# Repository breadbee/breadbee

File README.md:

# Breadbee

A very small, 32mm x 30mm, ARM Cortex A7 development board that costs about ~$10
to make in low quantities and can be assembled at home with a cheap hot air rework
station. With a [small adapter socket](./hivee) it can be mounted vertically in a standard breadboard.

The breadbee is based on a relatively unknown IP camera SoC, the MSC313E, from a company called MStar
(now part of MediaTek as a subsidiary called SigmaStar).
You might have never heard of MStar but you probably have one of their chips in your TV.

## Features

These are features that are working:

- ~1GHz Cortex A7 CPU with NEON etc[0].
- 64MB DDR2 (Probably DDR2-1333)
- 128KB SRAM (88KB if you use a MSC313(no e).
- [Bootable, memory mapped SPI-NOR](https://github.com/fifteenhex/linux/blob/msc313e/drivers/spi/spi-msc313-isp.c)
- 100Mbit ethernet.
- [4 x 10bit ADC channels](https://github.com/fifteenhex/linux/blob/msc313e/drivers/iio/adc/msc313e_sar.c)
- [2 x SPI](https://github.com/fifteenhex/linux/blob/msc313e/drivers/spi/spi-msc313.c)
- [1 x I2C (there is possibly one more)](https://github.com/fifteenhex/linux/blob/msc313e/drivers/i2c/busses/i2c-msc313e.c)
- [3 UARTs](https://github.com/fifteenhex/linux/blob/b3c521f8f30c9cc6f9f9c5c87429336d4756dcca/drivers/tty/serial/8250/8250_dw.c#L751) [1]
- Lots of GPIO. At least one pin with wake up support.
- [RTC](https://github.com/fifteenhex/linux/blob/msc313e/drivers/rtc/rtc-msc313e.c)
- [WDT](https://github.com/fifteenhex/linux/blob/msc313e/drivers/watchdog/msc313e_wdt.c)
- [3 x Timer](https://github.com/fifteenhex/linux/blob/msc313e/drivers/clocksource/timer-msc313e.c)
- [8 x PWM](https://github.com/fifteenhex/linux/blob/msc313e/drivers/pwm/pwm-msc313e.c)
- [SD/SDIO interface](https://github.com/fifteenhex/linux/blob/msc313e/drivers/mmc/host/mstar-fcie.c)
- 2 x ["byte" dma controller](https://github.com/fifteenhex/linux/blob/msc313e/drivers/dma/mstar/mstar-msc313-bdma.c)
- USB PHY
- USB host/device mux
- Faraday FUSBH200 USB *ehci* host controller
- On die temperature sensor. (sorta)
- Hardware RNG. (quality unknown)
- SHA engine. (Runs, not wired to the kernel)
- 8051 "house keeping" MCU. (Basic remoteproc driver)

[0] MStar says it's 800MHz but their own cpufreq code says they clock it to 1GHz
Clocking up to 1.1GHz works fine running dhrystone for hours but causes random lock ups if the spi nor controller and ethernet are fighting for bus access.
[1] One UART is used by the serial console, two more are available via muxing. 

 The chip has a bunch of stuff in it that isn't supported yet:
 - [MUSB USB device controller](https://github.com/fifteenhex/linux/blob/msc313e/drivers/usb/musb/mstar.c)
 - Camera interface, h264 encoder, mjpeg etc.
 - Audio ADC/DAC
 - [Crypto engine](https://github.com/fifteenhex/linux/blob/msc313e/drivers/crypto/msc313-aesdma.c) that seems to be able to do AES encrypted DMA transfers, memory mapped AES encryption etc
 - Some sort of IR decoder that can wake the chip up based on the IR codes it sees.
 - 6 byte unique device ID and efuse for key storage
 - [command queue dma controller](https://github.com/fifteenhex/linux/blob/msc313e/drivers/dma/mstar/mstar-msc313-cmdq.c)

It's full of flashy magic!

## Power consumption

According to a Kyoritsu KEW 1062 inline with the vbus of a usb cable:

| state        | Ethernet on | RTC wake | value |
|--------------|-------------|----------|-------|
| Booted idle  | yes         | N/A      | 138mA |
| Booted idle  | no          | N/A      | 113mA |
| Memory sleep |             | Yes      | 12mA  |

## Board Revisions

- Rev0 - Original version, works.
- Rev1 - Same as rev0 basically but the QFN80 footprint is slightly fixed to not have very thin pads on one side. Rev1 has one weird pad on the QFN80 footprint and an overlapping extra trace on one of the USB signals.

## Motivations

- Networked microcontrollers are a disaster waiting to happen; Many solutions - even commercial ones - use LWIP as the TCP/IP stack with no intention of actually maintaining it, use relatively unknown TLS libraries because of lack of memory, have no memory protection, no isolation between the moving parts.

- There are no solutions yet that can run a real OS like Linux that can be integrated by hobbyists into boards from cheap PCB vendors that don't have show stopping limitations. I.e. the AllWinner V3s is very similar to the SoC used here but it only has one SPI controller that is lost as soon as you put SPI NOR on it. The MSC313E has just enough of the usual microcontroller peripherals to make it useful, comes in a (relatively) easy to work with QFN package, is tiny and costs ~$4.
It is a bit harder to integrate into your designs than a microcontroller that requires a single power supply but all of the information you would need to do so is right here. The schematic for the breadbee is incredibly simple.

- There are single board computers out there that have more cores, more memory etc and are still around $10 but they are over kill for applications where even an ESP32 has enough horse power and they aren't usually something you can integrate into your project without reserving considerable space.

- Why not? The MSC313E is a Cortex-A so getting Linux running from scratch was relatively simple. The peripherals are super weird in places but not totally insane.

## But where's the WiFi!>!!111

The breadbee is meant to be a "minimum viable product" to get the ball rolling. It's impossible to write drivers for the SDIO controller or USB needed for WiFi without a platform to work on. Breadbee is that platform. Once SDIO works there will be an Ampak AP6212 based module to add wifi to breadbees and maybe a respin of the breadbee with the ethernet jack replaced with an Ampak module. 

A simpler alternative consists in using an already supported USB-to-WiFi PCB module given that the breadbee's USB host controller already works fine. This project is .

## Can I have one.. where do I get the chips..

- If you ask very nicely and you are willing to do something like write a nice python library or flesh out drivers for the board it's possible you can have one of the prototype boards for FREE! Get in touch!

- ~~If you just want to buy one the intention is to put the board up on a crowd sourcing site at some point. When that happens that information will be here.~~ [crowdsupply](https://www.crowdsupply.com/daniel-palmer/breadbee) will eventually be selling premade boards. This might take a while though.

- If you want chips to integrate into your own projects and don't have contacts in Shenzhen to get them get in touch and we'll figure something out. If you want 2080 of them getting them isn't a problem. If you want one or two I have a small supply. If the crowd sourcing happens and there is enough money left to buy extra chips to distribute in more accessible ways I will. Since April 2020 chips have now also started to turn on up ebay.

- The gerbers have been uploaded to [OSH park (rev1)](https://oshpark.com/shared_projects/lQ6wt3Dk) ready to order. [OSH park (rev0)](https://oshpark.com/shared_projects/slorKWK0)

## Software

Note that this is all in flux right at the moment. These repos are getting rebase'd fairly often.

### U-boot

There is a basic port of u-boot that so far take over from the MStar IPL and load a kernel from the SPI NOR, write it etc.
See boot process below for more details.

https://github.com/fifteenhex/u-boot/tree/msc313

### Kernel

All of the above features work to some degree in the work tree. Mainlining is in progress but will take time.
For more info please see the linux-chenxing.org [page about mainlining](http://linux-chenxing.org/mainlining.html).

### Buildroot

Combines the u-boot and kernel above with a root filesystem and generates flashable images.
There are some small pieces of a board configuration application called "beecfg" to setup pinmuxing etc.

https://github.com/fifteenhex/breadbee_buildroot

## BoM

[Google Sheet](https://docs.google.com/spreadsheets/d/1FwoQdfAULd6vKPnkrVnFDfQQs8OdsqdwefH3aLVehPo)

## Pin Table

### J2 - Main 2.54mm header

| interrupt | 5v tolerant |   notes   | alt functions           |    name   |  # |  # |   name    | alt functions           |   notes                 | 5v tolerant | interrupt |
|-----------|-------------|-----------|-------------------------|-----------|----|----|-----------|-------------------------|-------------------------|-------------|-----------|
|           |             |           |                         |    +5v    |  1 | 2  |   +3v3    |                         |                         |             |           |
|           |             |           |                         |    gnd    |  3 | 4  | pm_gpio4  |                         | [0]                     |    yes      |   yes     |
|           |             |           |                         | i2c1_scl  |  5 | 6  | i2c1_sda  |                         |                         |             |           |
|   yes     |             |           | ej_tck, pwm4            | spi0_cz   |  7 | 8  | spi0_ck   | ej_tms, pwm5            |                         |             |   yes     |
|   yes     |             |           | ej_tdo, pwm6            | spi0_di   |  9 | 10 | spi0_do   | ej_tdi, pwm7            |                         |             |   yes     |
|           |     yes     |           |                         | sar_gpio2 | 11 | 12 | sar_gpio3 |                         |                         |    yes      |           |
|           |     yes     |           |                         | sar_gpio1 | 13 | 14 | sar_gpio0 |                         |                         |    yes      |           |
|           |     yes     |   cs      | spi0_cz, pwm0           | fuart_rx  | 15 | 16 | fuart_tx  | spi0_ck, pwm1           |   clk                   |    yes      |           |
|           |     yes     | mosi, [1] | spi0_di, pwm2, uart1_rx | fuart_cts | 17 | 18 | fuart_rts | spi0_do, pwm3, uart1_tx |   miso                  |    yes      |           |
|           |             |           |                         | sr_io7    | 19 | 20 | sr_io6    |                         |                         |             |           |
|           |             |           |                         | sr_io5    | 21 | 22 | sr_io4    |                         |                         |             |           |
|           |             |           |                         | sr_io3    | 23 | 24 | sr_io2    |                         |                         |             |           |

0: This is a special pin that has to be explictly unlocked to be set. It seems to be intended for powering down the main CPU. It might move on rev1.

1 - When fuart is mux'd in it's also possible to mux'in uart1 and get a working rx only
    second uart here.

### J4 - Misc/High speed interfaces

* Note the USB and SD/SDIO are not guaranteed to work as literally no care was taken to route those signals properly on rev0. 

| name      | #  | alt functions | 5v tolerant | interrupt | notes |
|-----------|----|---------------|-------------|-----------|-------|
| +3v3      | 1  |               |             |           |       |
| sd_d3     | 2  |   spi1_do     | yes         |           | miso  |
| sd_d2     | 3  |   spi1_di     | yes         |           | mosi  |
| sd_d1     | 4  |   spi1_ck     | yes         |           | clk   |
| sd_d0     | 5  |   spi1_cz     | yes         |           | cs    |
| sd_cmd    | 6  |               | yes         |           |       |
| sd_clk    | 7  |               | yes         |           |       |
| pm_sd_cdz | 8  |               |             | yes       |       |
| gnd       | 9  |               |             |           |       |
| +5v       | 10 |               |             |           |       |
| usb_dm    | 11 |               |             |           |       |
| usb_dp    | 12 |               |             |           |       |
| gnd       | 13 |               |             |           |       |
| sr_io15   | 14 |               |             |           |       |
| sr_io14   | 15 |               |             |           |       |
| sr_io13   | 16 |               |             |           |       |
| sr_io12   | 17 |               |             |           |       |
| sr_io11   | 18 |               |             |           |       |
| sr_io10   | 19 |               |             |           |       |
| sr_io9    | 20 |               |             |           |       |
| sr_io8    | 21 |               |             |           |       |

### Test Points

- The audio pins are broken out to a series of test points on the left side of the parts size of the board.
- pm_irin is broken out to a test point on the ethernet jack side of the board.

## Using JTAG

JTAG is enabled at boot up on the spi0 pins by the u-boot SPL.

## More technical info

[linux-chenxing](http://linux-chenxing.org) has more info about mstar/sigmastar socs.

## Articles etc

[A nice blog entry from Willy about his experience building boards](https://wtarreau.blogspot.com/2020/09/breadbee-build-your-own-single-board.html)

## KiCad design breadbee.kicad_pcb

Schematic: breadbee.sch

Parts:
C1, C6, C9, C10, C11, C12, C13, C14, C15, C16, C17, C18, C19, C20, C21, C22, C24, C25, C26, C27, C35, C36, C37, C38: 1uf; C_0402_1005Metric
C2, C3, C4: 220pf; C_0402_1005Metric
C5: 1uF; C_0402_1005Metric
C7, C8: 18pf; C_0402_1005Metric
C23, C28, C29, C30, C31, C32: 10uf; C_0402_1005Metric
C33, C34: 100nf; C_0402_1005Metric
D1, D2: LED_Small; LED_0805_2012Metric
J1: HR961160C
J2: Conn_02x12_Odd_Even; PinHeader_2x12_P2.54mm_Vertical
J3: USB_B_Micro; USB-MICRO-B
J4: Conn_01x21; PinHeader_1x21_P1.00mm_Vertical
L1, L2, L3: 1.5uH; L_Taiyo-Yuden_MD-2020
R1: 200k; R_0402_1005Metric
R2, R3, R18, R21, R22: 100k; R_0402_1005Metric
R4: 150k; R_0402_1005Metric
R5: 510k; R_0402_1005Metric
R6: 110K; R_0402_1005Metric
R7: 1.1m; R_0402_1005Metric
R8, R19, R20: 1m; R_0402_1005Metric
R9, R10: 390; R_0402_1005Metric
R11, R12, R17: 0; R_0402_1005Metric
R13, R14, R15, R16: 22; R_0402_1005Metric
R23: 1.2m; R_0402_1005Metric
TP1, TP2, TP3, TP4, TP5, TP6, TP7: TestPoint; TestPoint_Pad_D1.0mm
U1: msc313e; QFN-80_EP_8x8_Pitch0.35mm
U2: spinor; wson8-8x6mm
U3: ea3036c; UQFN-20-1EP_3x3mm_P0.4mm_EP1.85x1.85mm_ThermalVias
U4: ch340e; MSOP-10_3x3mm_P0.5mm
U5: tvsarray; SOT-23-6
Y1: Crystal_GND24; Crystal_SMD_Abracon_ABM8G-4Pin_3.2x2.5mm

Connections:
+1V0: C3.1, C9.1, C10.1, C11.1, C12.1, C13.1, C20.1, C28.1, L3.2, R3.1, R21.1, U1.5, U1.8, U1.40, U1.60, U1.61, U1.67
+1V8: C2.1, C23.1, C24.1, C25.1, C26.1, L1.1, R1.1, R18.1, U1.3, U1.4, U1.6
+3V3: C4.1, C5.1, C6.1, C14.1, C15.1, C16.1, C17.1, C18.1, C19.1, C29.1, C37.1, J2.2, J4.1, L2.2, R5.1, R11.1, R12.1, R22.1, U1.7, U1.14, U1.27, U1.35, U1.43, U1.62, U2.7, U2.8, U4.7, U4.10, U5.5
+5V: C27.1, C30.1, C31.1, C32.1, J2.1, J3.1 (VBUS), J4.10, R7.1, R19.1, R20.1, U3.7, U3.10, U3.16, U3.19
/console_rx: U1.19, U4.9
/console_tx: U1.18, U4.8
/eth_rn: R15.2, U1.31
/eth_rp: R16.2, U1.32
/eth_tn: R13.2, U1.33
/eth_tp: R14.2, U1.34
/fuart_cts: J2.17, U1.38
/fuart_rts: J2.18, U1.39
/fuart_rx: J2.15, U1.36
/fuart_tx: J2.16, U1.37
/i2c1_scl: J2.5, U1.41
/i2c1_sda: J2.6, U1.42
/led0: R9.1, U1.58
/led1: R10.1, U1.59
/pm_gpio4: J2.4, U1.21
/pm_sd_cdz: J4.8, U1.15
/reset: C37.2, R23.1, U1.17
/sar_gpio0: J2.14, U1.12
/sar_gpio1: J2.13, U1.11
/sar_gpio2: J2.11, U1.10
/sar_gpio3: J2.12, U1.9
/sd_clk: J4.7, U1.68
/sd_cmd: J4.6, U1.69
/sd_d0: J4.5, U1.70
/sd_d1: J4.4, U1.71
/sd_d2: J4.3, U1.72
/sd_d3: J4.2, U1.73
/spi0_ck: J2.8, U1.64
/spi0_cz: J2.7, U1.63
/spi0_di: J2.9, U1.65
/spi0_do: J2.10, U1.66
/spinor_miso: U1.25, U2.2
/spinor_mosi: U1.23, U2.5
/spinor_sck: U1.26, U2.6
/spinor_~cs: U1.22, U2.1
/spinor_~wp: U1.24, U2.3
/sr_io2: J2.24, U1.44
/sr_io3: J2.23, U1.45
/sr_io4: J2.22, U1.46
/sr_io5: J2.21, U1.47
/sr_io6: J2.20, U1.48
/sr_io7: J2.19, U1.49
/sr_io8: J4.21, U1.50
/sr_io9: J4.20, U1.51
/sr_io10: J4.19, U1.52
/sr_io11: J4.18, U1.53
/sr_io12: J4.17, U1.54
/sr_io13: J4.16, U1.55
/sr_io14: J4.15, U1.56
/sr_io15: J4.14, U1.57
/usb_dm: J4.11, U1.75
/usb_dp: J4.12, U1.76
/xtal_in: C7.1, R8.2, U1.28, Y1.1
/xtal_out: C8.1, R8.1, U1.29, Y1.3
GND: C1.2, C5.2, C6.2, C7.2, C8.2, C9.2, C10.2, C11.2, C12.2, C13.2, C14.2, C15.2, C16.2, C17.2, C18.2, C19.2, C20.2, C21.2, C22.2, C23.2, C24.2, C25.2, C26.2, C27.2, C28.2, C29.2, C30.2, C31.2, C32.2, C33.2, C34.2, C35.2, C36.2, C38.2, D1.1, D2.1, J2.3, J3.5 (GND), J4.9, J4.13, R2.2, R4.2, R6.2, R17.2, R18.2, R21.2, R22.2, R23.2, U1.20, U1.81, U2.4, U3.1, U3.4, U3.5, U3.12, U3.13, U3.15, U3.17, U3.21, U4.3, U5.2, Y1.2, Y1.4
unnamed: C1.1, R7.2, U3.18
unnamed: C2.2, R1.2, R2.1, U3.14
unnamed: C3.2, R3.2, R4.1, U3.2
unnamed: C4.2, R5.2, R6.1, U3.3
unnamed: C21.1, R11.2, U1.30
unnamed: C22.1, R12.2, U1.74
unnamed: C33.1, J1.5
unnamed: C34.1, J1.6
unnamed: C35.1, R19.2, U3.9
unnamed: C36.1, R20.2, U3.8
unnamed: C38.1, U1.13
unnamed: D1.2, R9.2
unnamed: D2.2, R10.2
unnamed: J1.3, R14.1, U5.4
unnamed: J1.4, R13.1, U5.6
unnamed: J1.7, R16.1, U5.1
unnamed: J1.8, R15.1, U5.3
unnamed: J1.10, R17.1
unnamed: J3.2 (D-), U4.2
unnamed: J3.3 (D+), U4.1
unnamed: L1.2, U3.11
unnamed: L2.1, U3.6
unnamed: L3.1, U3.20
unnamed: TP1.1, U1.77
unnamed: TP2.1, U1.2
unnamed: TP3.1, U1.78
unnamed: TP4.1, U1.79
unnamed: TP5.1, U1.80
unnamed: TP6.1, U1.1
unnamed: TP7.1, U1.16

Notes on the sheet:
CONSOLE
STATUS LEDS
RESET
yes, reset is active high, this is not a mistake
24MHZ OSC
SPI NOR
USER IO
POWER SUPPLY
ETHERNET
DECOUPLING
These are jumpers to allow the usb and eth power supplies to be disconnected if you don't need them. This seems to actually stop the board from booting though so they might be removed in the next revision.
The enables are configured to sequence the power rails in accordance with the datasheet.

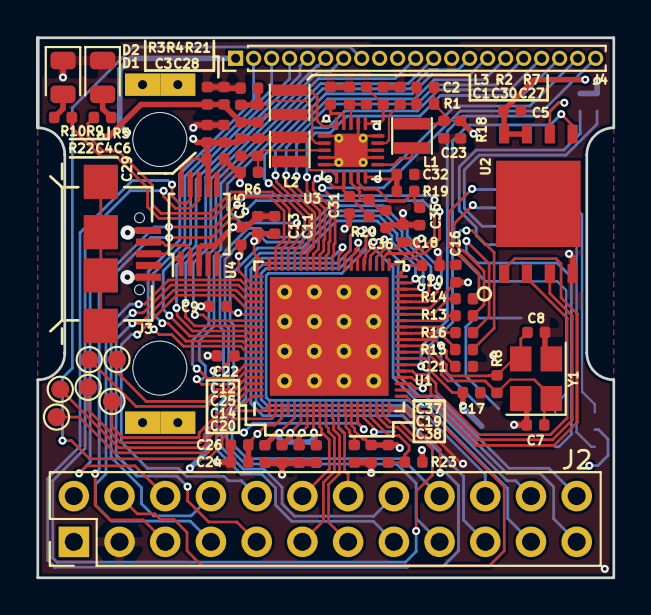
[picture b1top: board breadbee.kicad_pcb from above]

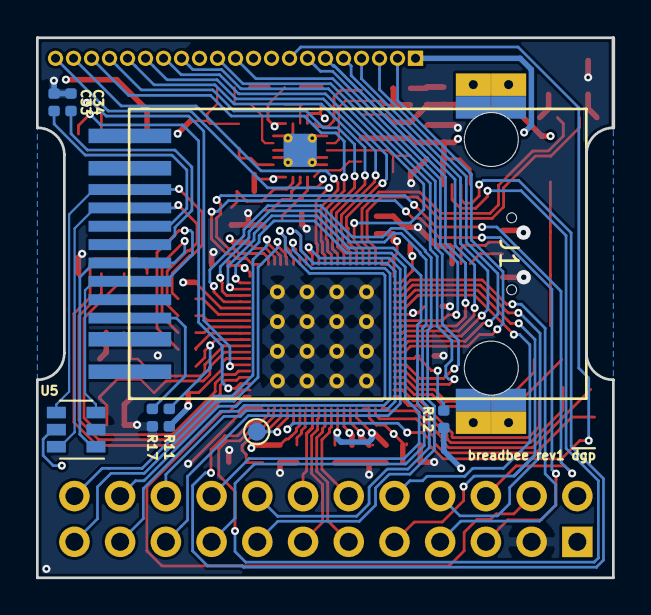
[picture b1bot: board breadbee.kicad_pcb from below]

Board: 4 copper layers, 32.0 x 30.0 mm, 83 parts (8 on the bottom side), 89 nets.

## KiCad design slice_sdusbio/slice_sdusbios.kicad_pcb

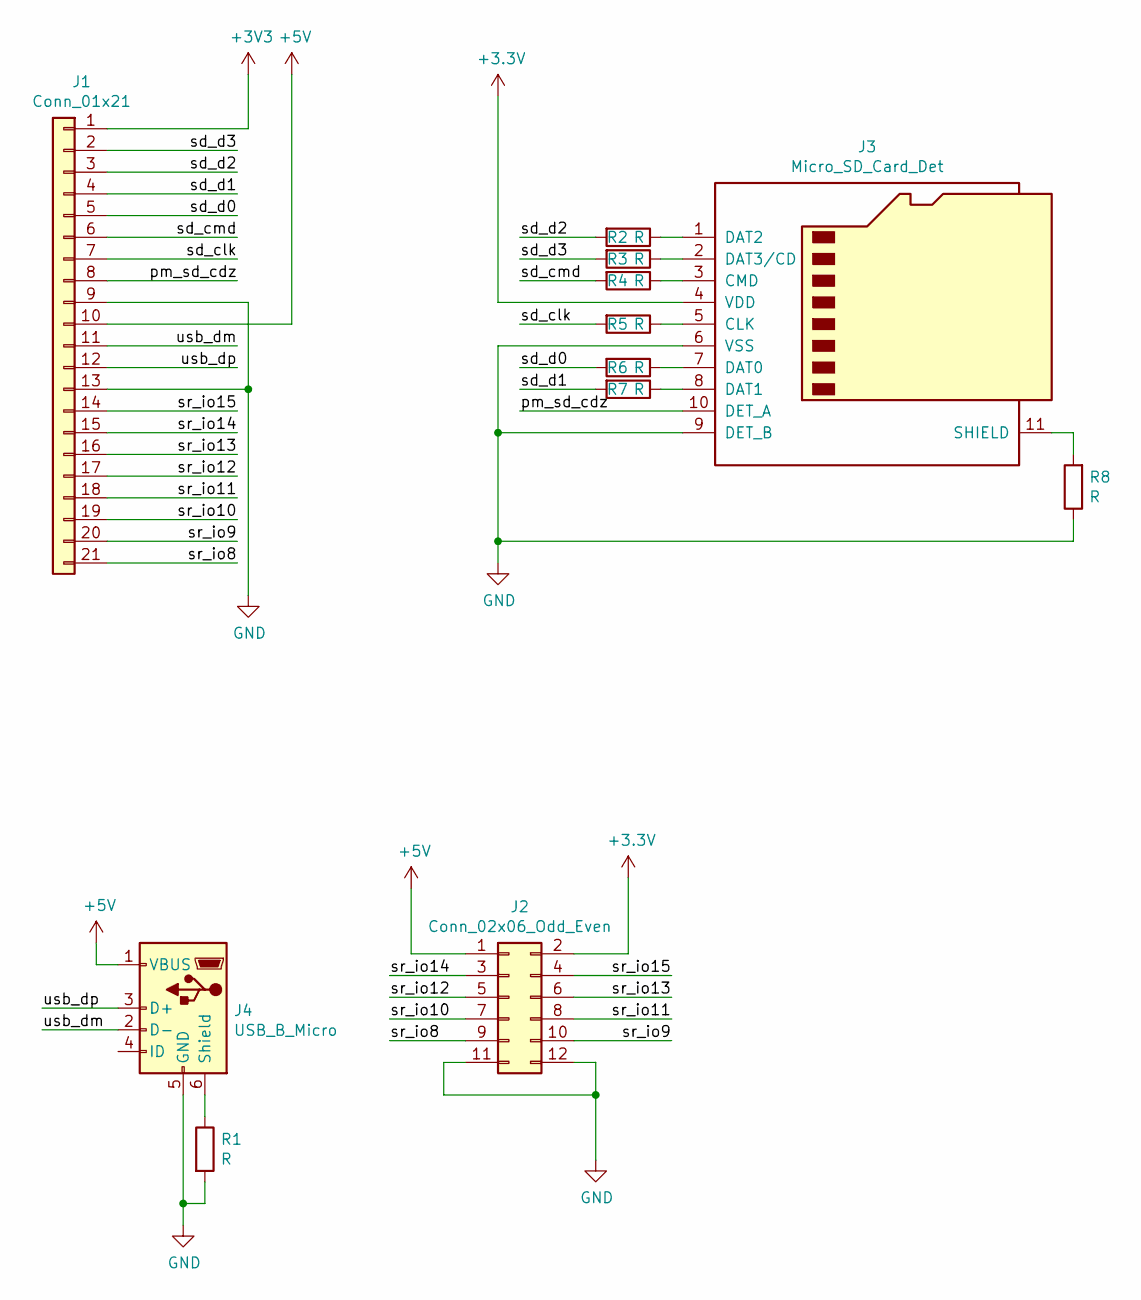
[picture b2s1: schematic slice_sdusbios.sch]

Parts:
J1: Conn_01x21; breadbee_1mm_header_connector
J2: Conn_02x06_Odd_Even; PinHeader_2x06_P2.54mm_Vertical
J3: Micro_SD_Card_Det; 47309-2651
J4: USB_B_Micro; USB-MICRO-B
R1, R2, R3, R4, R5, R6, R7, R8: R; R_0402_1005Metric

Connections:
+5V: J1.10, J2.1, J4.1 (VBUS)
/pm_sd_cdz: J1.8, J3.10 (DET_A)
/sd_clk: J1.7, R5.2
/sd_cmd: J1.6, R4.2
/sd_d0: J1.5, R6.2
/sd_d1: J1.4, R7.2
/sd_d2: J1.3, R2.2
/sd_d3: J1.2, R3.2
/sr_io8: J1.21, J2.9
/sr_io9: J1.20, J2.10
/sr_io10: J1.19, J2.7
/sr_io11: J1.18, J2.8
/sr_io12: J1.17, J2.5
/sr_io13: J1.16, J2.6
/sr_io14: J1.15, J2.3
/sr_io15: J1.14, J2.4
/usb_dm: J1.11, J4.2 (D-)
/usb_dp: J1.12, J4.3 (D+)
GND: J1.9, J1.13, J2.11, J2.12, J3.6 (VSS), J3.9 (DET_B), J4.5 (GND), R1.2, R8.1
unnamed: J3.1 (DAT2), R2.1
unnamed: J3.2 (DAT3/CD), R3.1
unnamed: J3.3 (CMD), R4.1
unnamed: J3.5 (CLK), R5.1
unnamed: J3.7 (DAT0), R6.1
unnamed: J3.8 (DAT1), R7.1
unnamed: J3.11 (SHIELD), R8.2
unnamed: J4.6 (Shield), R1.1

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
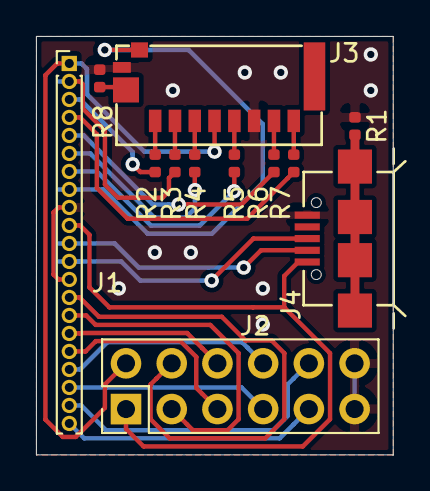
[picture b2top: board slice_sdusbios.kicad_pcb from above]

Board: 2 copper layers, 19.8 x 23.2 mm, 12 parts (0 on the bottom side), 28 nets.

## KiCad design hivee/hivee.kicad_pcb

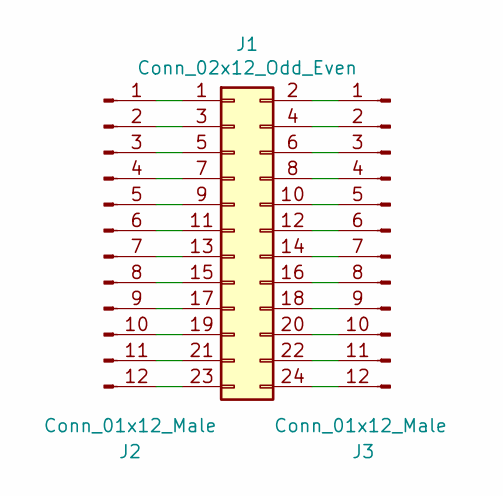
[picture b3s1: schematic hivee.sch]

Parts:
J1: Conn_02x12_Odd_Even; PinSocket_2x12_P2.54mm_Vertical
J2, J3: Conn_01x12_Male; PinHeader_1x12_P2.54mm_Vertical

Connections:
unnamed: J1.1, J2.1
unnamed: J1.2, J3.1
unnamed: J1.3, J2.2
unnamed: J1.4, J3.2
unnamed: J1.5, J2.3
unnamed: J1.6, J3.3
unnamed: J1.7, J2.4
unnamed: J1.8, J3.4
unnamed: J1.9, J2.5
unnamed: J1.10, J3.5
unnamed: J1.11, J2.6
unnamed: J1.12, J3.6
unnamed: J1.13, J2.7
unnamed: J1.14, J3.7
unnamed: J1.15, J2.8
unnamed: J1.16, J3.8
unnamed: J1.17, J2.9
unnamed: J1.18, J3.9
unnamed: J1.19, J2.10
unnamed: J1.20, J3.10
unnamed: J1.21, J2.11
unnamed: J1.22, J3.11
unnamed: J1.23, J2.12
unnamed: J1.24, J3.12

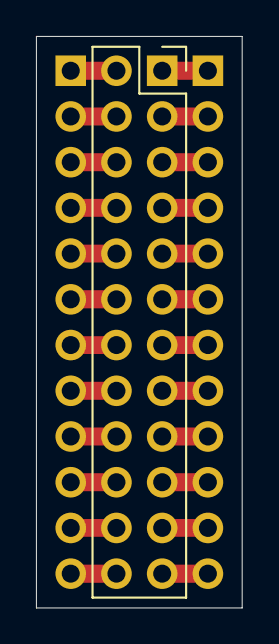
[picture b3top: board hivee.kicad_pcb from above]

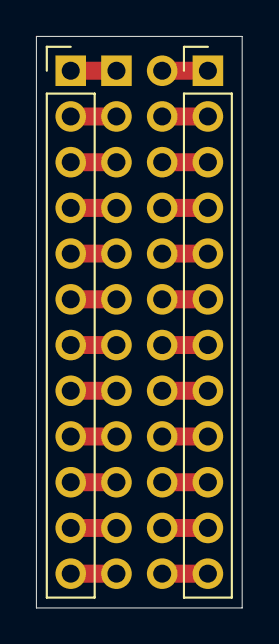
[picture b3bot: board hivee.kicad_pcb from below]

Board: 2 copper layers, 11.4 x 31.8 mm, 3 parts (2 on the bottom side), 24 nets.

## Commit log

2019-05-13 rev0: renders
2019-05-24 rev0
2019-05-24 Everyone loves a readme
2019-05-24 Add pin table for j2
2019-05-30 Fix some component values
2019-06-10 Add layout file for flashrom used to replace firmware bits. Add openocd config file.
2019-06-14 Fix screw up with the sar pins
2019-06-15 Clean up schematic. Add PDF plot of schematic.
2019-06-18 Add a blinky gif
2019-06-19 Add hivee breadboard adapter
2019-07-09 Add scan of board
2019-07-09 Move component side board scan into sub directory
2019-07-10 Add links to relevant drivers
2019-07-10 Add small 1mm -> 2.54mm break out.
2019-09-03 USB SDIO io breakout
2019-09-03 Fix solder mask.
2019-12-02 USB works now.
2020-04-14 Add link to linux-chenxing
2020-04-20 Add missing symbol/footprint tables
    The repository is missing the fp-lib-table and sym-lib-table files which
    makes problems when editing/viewing schematics on freshly cloned repo.
    The provided tables uses ${KIPRJMOD} to be independent from the path in
    the file system.
2020-04-20 pcb: fix the sloppy solder mask
2020-04-20 pcb/footprint: fix up the thin pins on the soc
2020-04-20 sch: add missing values
2020-04-20 Add the usb/sd card breakout
2020-04-23 Missing values, public bom link
2020-06-07 Move how to build
2020-06-07 rev 1+ - fix another weird pad
2020-06-07 howtobuild: images
2020-06-25 pcb: remove redundant fragment of usb_dp
    On a wire connecting the usb_dp to the header pin there was a redundant
    fragment that was going on top of the actual wire connecting the whole
    net. A small part of this wire had an offset making the wire ticker in
    one place as well.
    I noticed that by pure luck by manually going over the wire (after
    pressing I). Unfortunately I don't know any method of automatically
2020-06-25 footprints: fix courtyard of wson8-8x6mm
    One edge (left one) of the courtyard box in this package was drawn on
    the wrong layer (Dwgs.User instead of F.CrtYd) like others. While
    hard/impossible to see by an eye, for the Kicad this was unclosed shape
    making it complain in DRC if courtyard checks are enabled.
    Note that in order to make this change small and easy to merge in case
    of conflicts, I did not include the change on the kicad_pcb file after
2020-06-25 footprints: fix courtyard width on wson8-8x6mm
    While I was editing the courtyard of this footprint I noticed that it
    has a default width of 0.15mm. The Kicad Library Conventions point 5.3
    (https://kicad-pcb.org/libraries/klc/F5.3/) specifies, however, that
    courtyard with should be 0.05mm
2020-06-28 Attempting to CI this
2020-06-28 Try to use pcbdraw
2020-06-28 Use debian sid
2020-06-28 Add a makefile to render outputs
2020-06-28 Publish the rendered files
2020-07-04 howtobuild: provide a printable reference for components
    This adds:
    - components-layout.svg : source file (inkscape)
    - components-only.pdf : components only, printable format
    - components-copper.jpg : components on top of copper tracks
    - components-photo.jpg : components on top of finished board photo
    howtobuild was updated to mention it.
2020-07-11 howtobuild: update the components layout
    - D2 (top left) is the yellow LED
    - D1 (right) is the red LED
    Also added locations of a few reference voltages to ease debugging.
2020-08-18 Add swanky ibom
2020-08-22 Move the addons out into their own repo: https://github.com/breadbee/breadbee_addons
2020-08-24 addons: add info about how to easily add a cheap WiFi module
    It's particularly easy to add WiFi support to the breadbee, so let's
    document how this can be done, providing configs, patches, schematics,
    boards and photos.
2020-08-24 addons: Fix a minor typo.
